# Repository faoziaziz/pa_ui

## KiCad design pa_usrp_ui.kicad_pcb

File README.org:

#+title: PA Usrp UI

* Simulasi

Silahkan ada di direktory simulasi perhatikan bahwa file xmlnya perlu untuk
diupdate.

dan unutk menjalankan simulasinya gunakan perintah berikut

#+begin_src
rm -rf sim_J1_RFIN
rm -f pa_rfin_results.mat
octave --quiet pa_openems.m
#+end_src

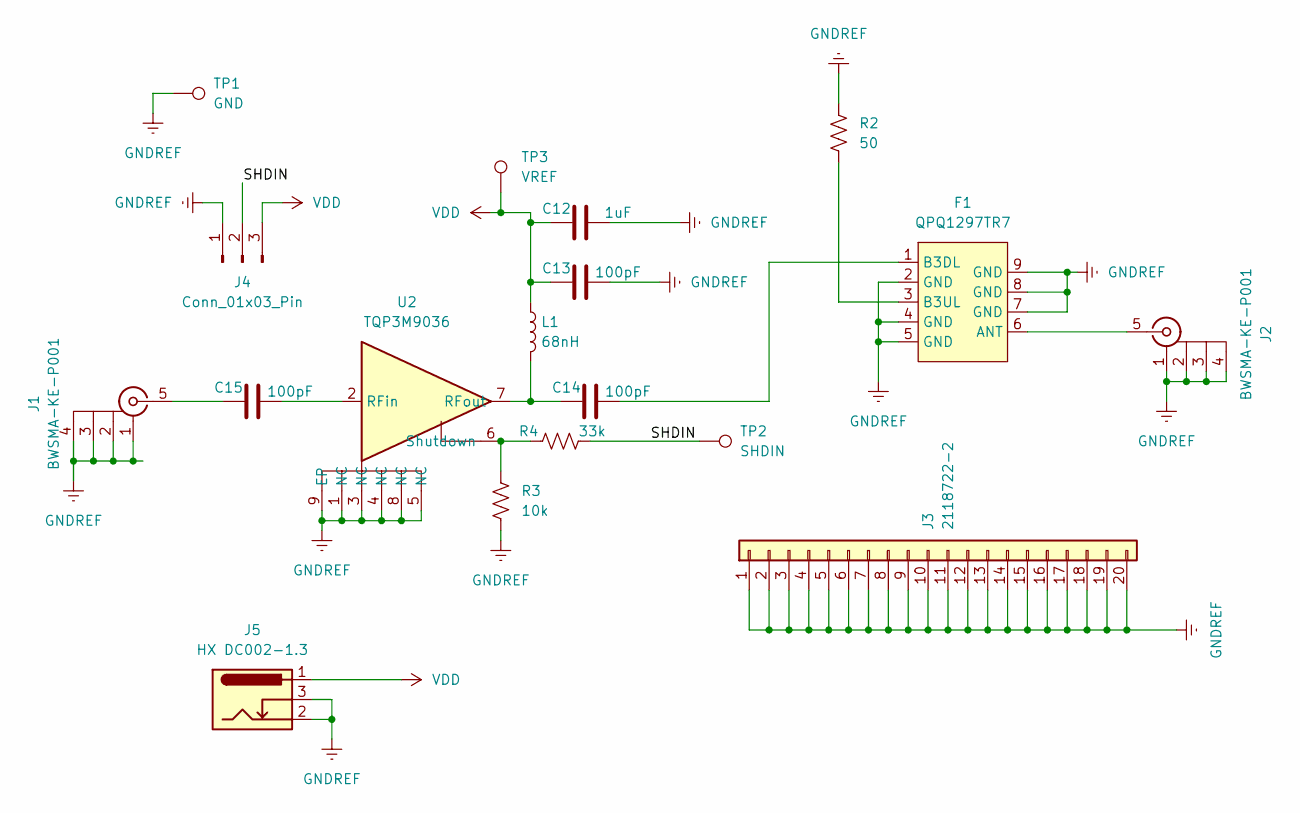
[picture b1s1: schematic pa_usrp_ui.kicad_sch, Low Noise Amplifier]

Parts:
C12: 1uF; C_0402_1005Metric; lcsc_id C52923
C13, C14, C15: 100pF; C_0402_1005Metric; lcsc_id C1546
F1: QPQ1297TR7; FILTER-SMD_9P-L2.5-W2.0-BL_QPQ1297TR7; lcsc_id C471170
J1, J2: BWSMA-KE-P001; SMA-SMD_BWSMA-KE-P001; lcsc_id C496550
J3: 2118722-2; CONN-SMD_2118722-2; lcsc_id C5371638
J4: Conn_01x03_Pin; PinHeader_1x03_P2.54mm_Vertical
J5: HX DC002-1.3; DC-IN-TH_HANXIA_HX-DC002-1.3; lcsc_id C5184827
L1: 68nH; L_0603_1608Metric; lcsc_id C6364697
R2: 50; R_0603_1608Metric; lcsc_id C849792
R3: 10k; R_0603_1608Metric; lcsc_id C25804
R4: 33k; R_0603_1608Metric; lcsc_id C4216
TP1: GND; TestPoint_Pad_D2.5mm
TP2: SHDIN; TestPoint_Pad_D2.5mm
TP3: VREF; TestPoint_Pad_D2.5mm
U2: TQP3M9036; DFN-8_L2.0-W2.0-P0.50-BL-EP; lcsc_id C920261

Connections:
/SHDIN: J4.2, R4.2, TP2.1 (1_1)
GNDREF: C12.2, C13.2, F1.2 (GND), F1.4 (GND), F1.5 (GND), F1.7 (GND), F1.8 (GND), F1.9 (GND), J1.1, J1.2, J1.3, J1.4, J2.1, J2.2, J2.3, J2.4, J3.1, J3.2, J3.3, J3.4, J3.5, J3.6, J3.7, J3.8, J3.9, J3.10, J3.11, J3.12, J3.13, J3.14, J3.15, J3.16, J3.17, J3.18, J3.19, J3.20, J4.1, J5.2, J5.3, R2.1, R3.2, TP1.1 (1_1), U2.1 (NC), U2.3 (NC), U2.4 (NC), U2.5 (NC), U2.8 (NC), U2.9 (EP)
unnamed: C15.1, J1.5
unnamed: F1.6 (ANT), J2.5
unnamed: C14.2, F1.1 (B3DL)
unnamed: F1.3 (B3UL), R2.2
unnamed: C15.2, U2.2 (RFin)
unnamed: C14.1, L1.2, U2.7 (RFout)
unnamed: R3.1, R4.1, U2.6 (Shutdown)
VDD: C12.1, C13.1, J4.3, J5.1, L1.1, TP3.1 (1_1)

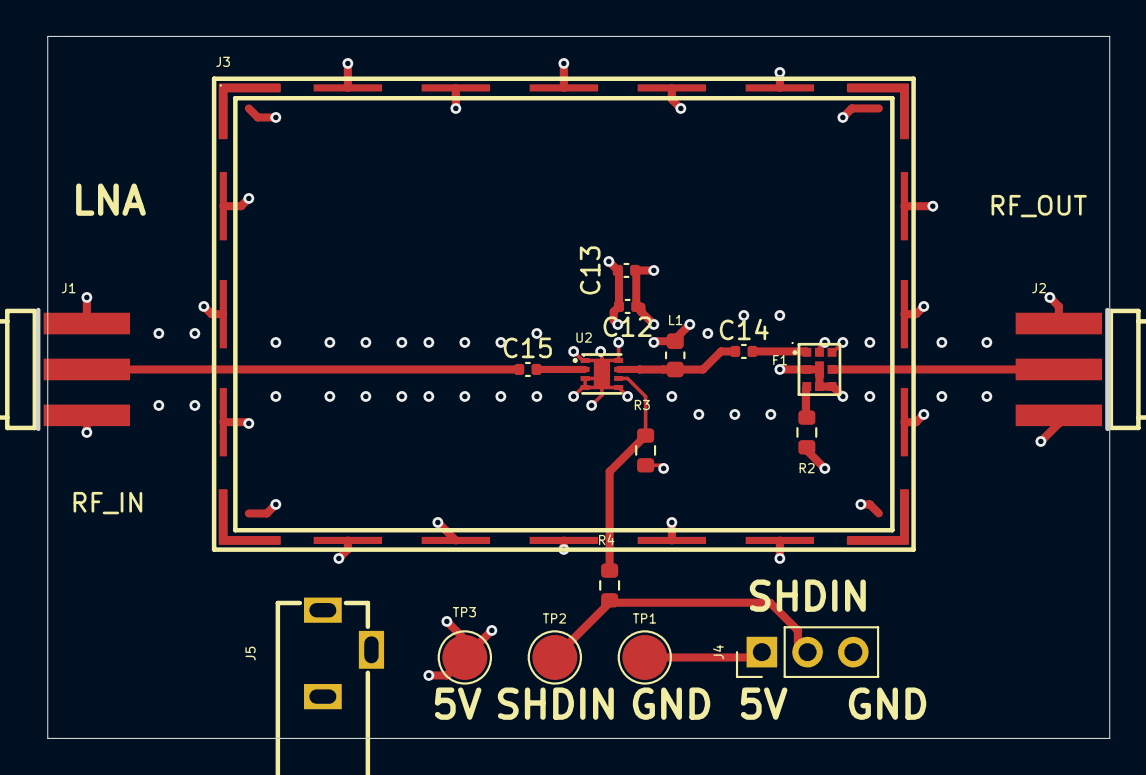
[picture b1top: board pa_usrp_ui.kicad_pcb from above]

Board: 4 copper layers, 59.5 x 39.0 mm, 18 parts (0 on the bottom side), 10 nets.

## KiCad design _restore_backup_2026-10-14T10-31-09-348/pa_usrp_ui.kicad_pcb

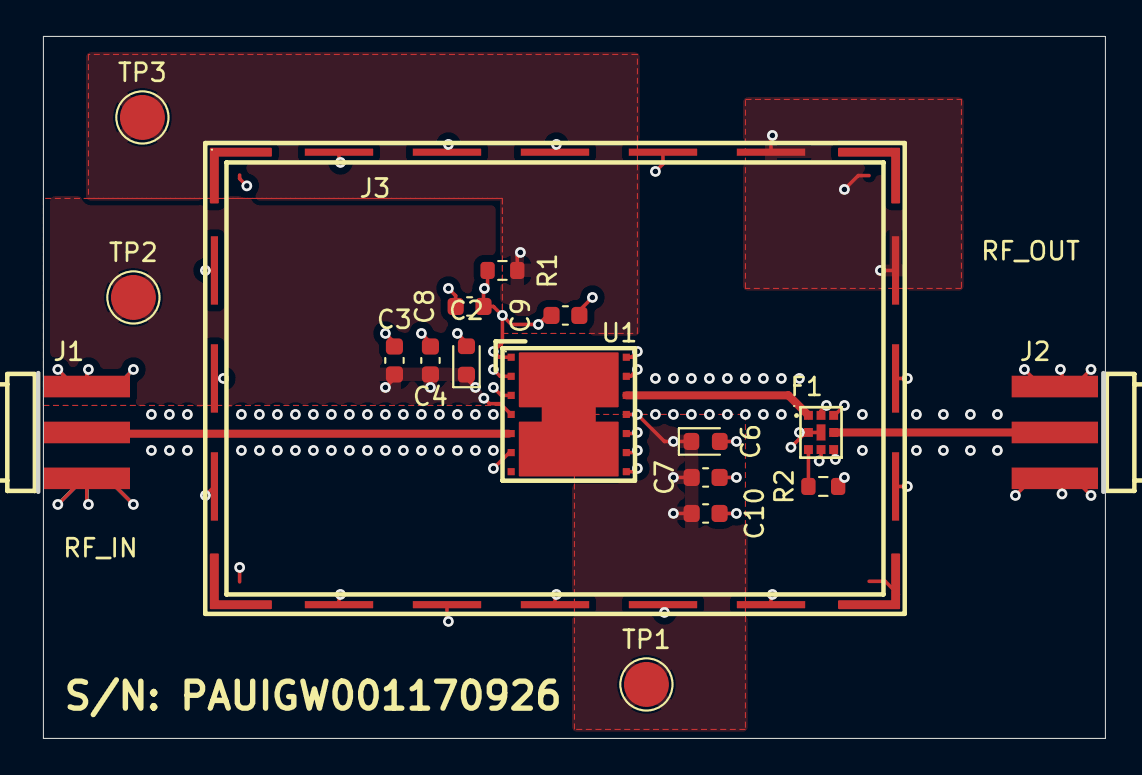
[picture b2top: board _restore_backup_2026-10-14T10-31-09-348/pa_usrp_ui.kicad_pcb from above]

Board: 4 copper layers, 59.0 x 39.0 mm, 18 parts (0 on the bottom side), 9 nets.

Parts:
C2, C6: 10.0uF; D_0603_1608Metric
C3, C9, C10: 0.1uF; C_0603_1608Metric
C4, C7: 1000pF; C_0603_1608Metric
C8: 100pF; C_0603_1608Metric
F1: QPQ1297TR7; FILTER-SMD_9P-L2.5-W2.0-BL_QPQ1297TR7
J1, J2: BWSMA-KE-P001; SMA-SMD_BWSMA-KE-P001
J3: 2118722-2; CONN-SMD_2118722-2
R1: 0; R_0603_1608Metric
R2: 50; R_0603_1608Metric
TP1: VCC1; TestPoint_Pad_D2.5mm
TP2: VCC2; TestPoint_Pad_D2.5mm
TP3: VREF; TestPoint_Pad_D2.5mm
U1: QPA9418TR13; DFN-14_L7.0-W7.0-P1.06-TL-EP_QPA9418TR13

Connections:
GNDREF: C2.2, C3.2, C4.2, C6.2, C7.2, C8.2, C9.2, C10.2, F1.2 (GND), F1.4 (GND), F1.5 (GND), F1.7 (GND), F1.8 (GND), F1.9 (GND), J1.1, J1.2, J1.3, J1.4, J2.1, J2.2, J2.3, J2.4, J3.1, J3.2, J3.3, J3.4, J3.5, J3.6, J3.7, J3.8, J3.9, J3.10, J3.11, J3.12, J3.13, J3.14, J3.15, J3.16, J3.17, J3.18, J3.19, J3.20, R2.1, U1.2 (GND), U1.3 (GND), U1.6 (GND), U1.8 (GND), U1.9 (GND), U1.10 (GND), U1.13 (GND), U1.14 (GND)
unnamed: F1.6 (ANT), J2.5
unnamed: F1.1 (B3DL), U1.12 (RFOUT)
unnamed: F1.3 (B3UL), R2.2
unnamed: J1.5, U1.5 (RFIN)
unnamed: C8.1, C9.1, R1.2, U1.1 (VREF)
VCC1: C2.1, C3.1, C4.1, TP2.1 (1_1), U1.4 (VCC1)
VCC2: C6.1, C7.1, C10.1, TP1.1 (1_1), U1.11 (VCC2)
VREF: R1.1, TP3.1 (1_1)
